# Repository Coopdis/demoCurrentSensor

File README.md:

# demoCurrentSensor
An IoT current sensor for household use

This is a demo designed to showcase some of my development skill.

It is more of a toy than a product.

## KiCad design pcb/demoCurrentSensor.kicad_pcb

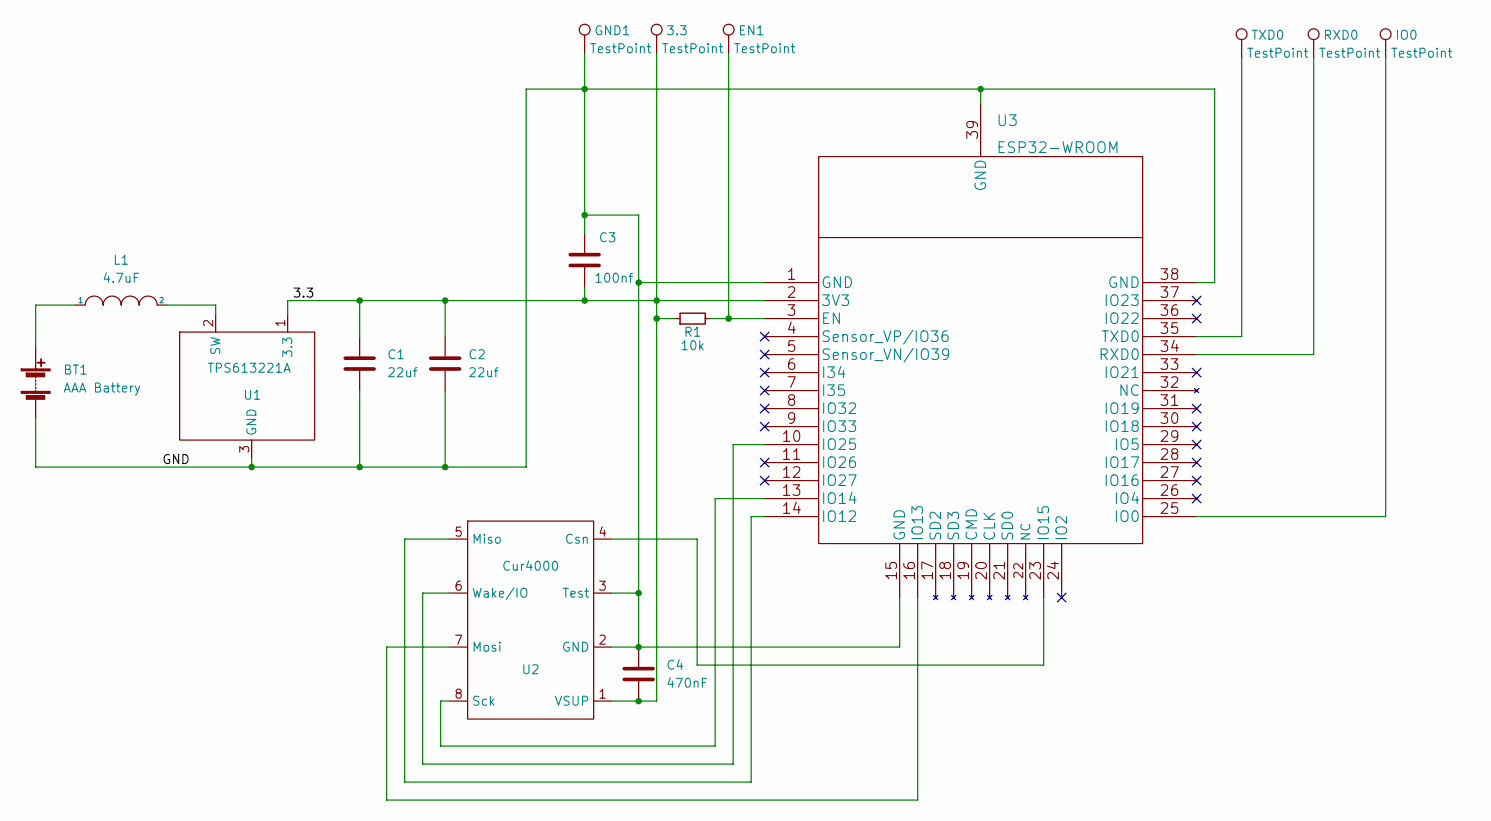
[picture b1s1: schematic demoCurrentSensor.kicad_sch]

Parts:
3.3: TestPoint; TestPoint_Pad_D1.5mm
BT1: AAA Battery; BatteryHolder_Keystone_2466_1xAAA
C1, C2: 22uf; C_0805_2012Metric
C3: 100nf; C_0603_1608Metric
C4: 470nF; C_0603_1608Metric
EN1: TestPoint; TestPoint_Pad_D1.5mm
GND1: TestPoint; TestPoint_Pad_D1.5mm
IO0: TestPoint; TestPoint_Pad_D1.5mm
L1: 4.7uF; L_Bourns-SRN4018
R1: 10k; R_0603_1608Metric
RXD0: TestPoint; TestPoint_Pad_D1.5mm
TXD0: TestPoint; TestPoint_Pad_D1.5mm
U1: TPS613221A; SOT-23
U2: Cur4000; SOIC-8-1EP_3.9x4.9mm_P1.27mm
U3: ESP32-WROOM; ESP32-WROOM-32E

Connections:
/3.3: 3.3.1, C1.1, C2.1, C3.1, C4.2, R1.1, U1.1 (3.3), U2.1 (VSUP), U3.2 (3V3)
/GND: BT1.2 (-), C1.2, C2.2, C3.2, C4.1, GND1.1, U1.3 (GND), U2.2 (GND), U2.3 (Test), U3.1 (GND), U3.15 (GND), U3.38 (GND), U3.39 (GND)
unnamed: BT1.1 (+), L1.1
unnamed: EN1.1, R1.2, U3.3 (EN)
unnamed: IO0.1, U3.25 (IO0)
unnamed: L1.2, U1.2 (SW)
unnamed: RXD0.1, U3.34 (RXD0)
unnamed: TXD0.1, U3.35 (TXD0)
unnamed: U2.4 (Csn), U3.23 (IO15)
unnamed: U2.5 (Miso), U3.14 (IO12)
unnamed: U2.6 (Wake/IO), U3.10 (IO25)
unnamed: U2.7 (Mosi), U3.16 (IO13)
unnamed: U2.8 (Sck), U3.13 (IO14)

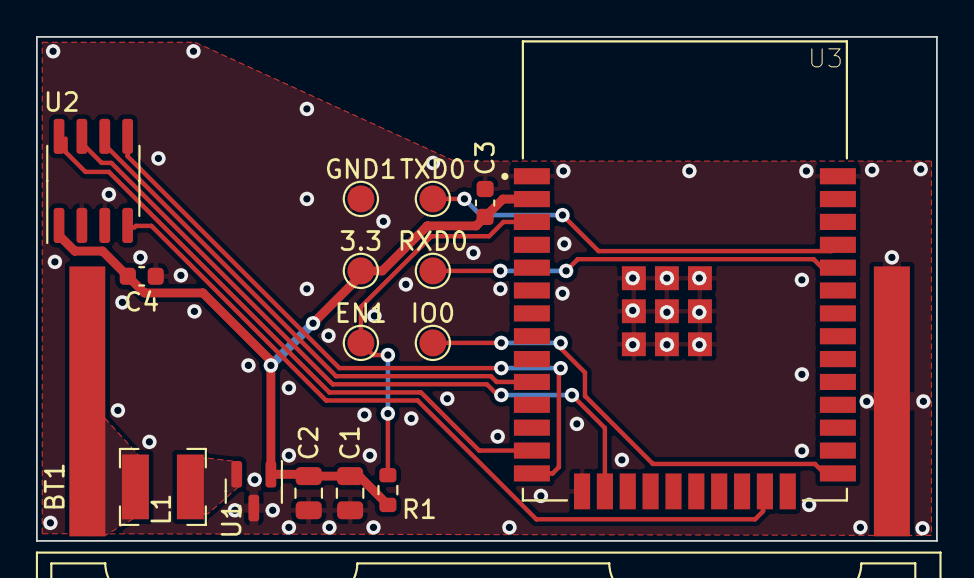
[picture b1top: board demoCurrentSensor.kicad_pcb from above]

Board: 2 copper layers, 50.0 x 28.0 mm, 16 parts (0 on the bottom side), 13 nets.

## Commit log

2024-07-02 Initial Schematic
2024-07-03 PCB design progress
2024-07-04 PCB routing
2024-07-05 initial
2024-07-05 tuning solidworks
